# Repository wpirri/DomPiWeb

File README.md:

# DomPiWeb
 Sistema de Domótica con central domiciliaria basada en Raspberry Pi y servicios en la nube para administración externa remota.

 El sistema está formado por una serie de programas en c y c++ que se ejecutan
 dentro del monitor transaccional GMonitor y todo el sistema preparado para
 funcionar en una Raspberry Pi o distribuido entre varias.
 Otro módulo del sistema funciona en un servidor Linux centralizando varios sistemas hogareños permitiendo el acceso remoto a travez de la nube.
 
## Componentes del sistema:
### DomPiWeb: Central domiciliaria de Domótica.
El proyecto contiene distintos programas que se ejecutan como servers dentro de un monitor transaccional GMonitor (https://github.com/wpirri/gmonitor), CGI para hacer de interface con Apache y un micrositio en PHP para la administración local todo este software se ejecuta en una Raspberry Pi. Se incluye además un harware para ser enchufado en el conector de 40 pines de la Raspberry Pi, aprovechar algunos pines de la GPIO y darle alimentación. También se encuentra dentro del proyecto los diseños para imprimir un gabinete para contener la central de domótica y otro para su taería con cargador.

### DomPiIO: Software que permite utilizar la Rasberri Pi como un módulo de expanción de la central de Domótica o como Central de Alarmas integrada al Sistema de Domótica.
El proyecto (https://github.com/wpirri/DomPiIO) contiene distintos programas que se ejecutan como servers dentro de un monitor transaccional GMonitor (https://github.com/wpirri/gmonitor) y CGI para hacer de interface con Apache.

### DomPiClowd: Software que permite controlar los sistemas hogareños desde la nobe.
El proyecto (https://github.com/wpirri/DomPiClowd) contiene distintos programas que se ejecutan como servers dentro de un monitor transaccional GMonitor (https://github.com/wpirri/gmonitor), CGI y un micrositio en PHP para el control de los sistemas de domótica desde un teléfono celular.

### dom32-io-wifi: Harware de módulo de expansió para central de domótica.
El proyecto (https://github.com/wpirri/dom32-io-wifi) está compuesto por un Hardware basado en PIC32 que por medio de servicios REST implementa una interface con la central de domótica DomPiWeb, el firmware necesario y el diseño del gabinete para contenerlo.

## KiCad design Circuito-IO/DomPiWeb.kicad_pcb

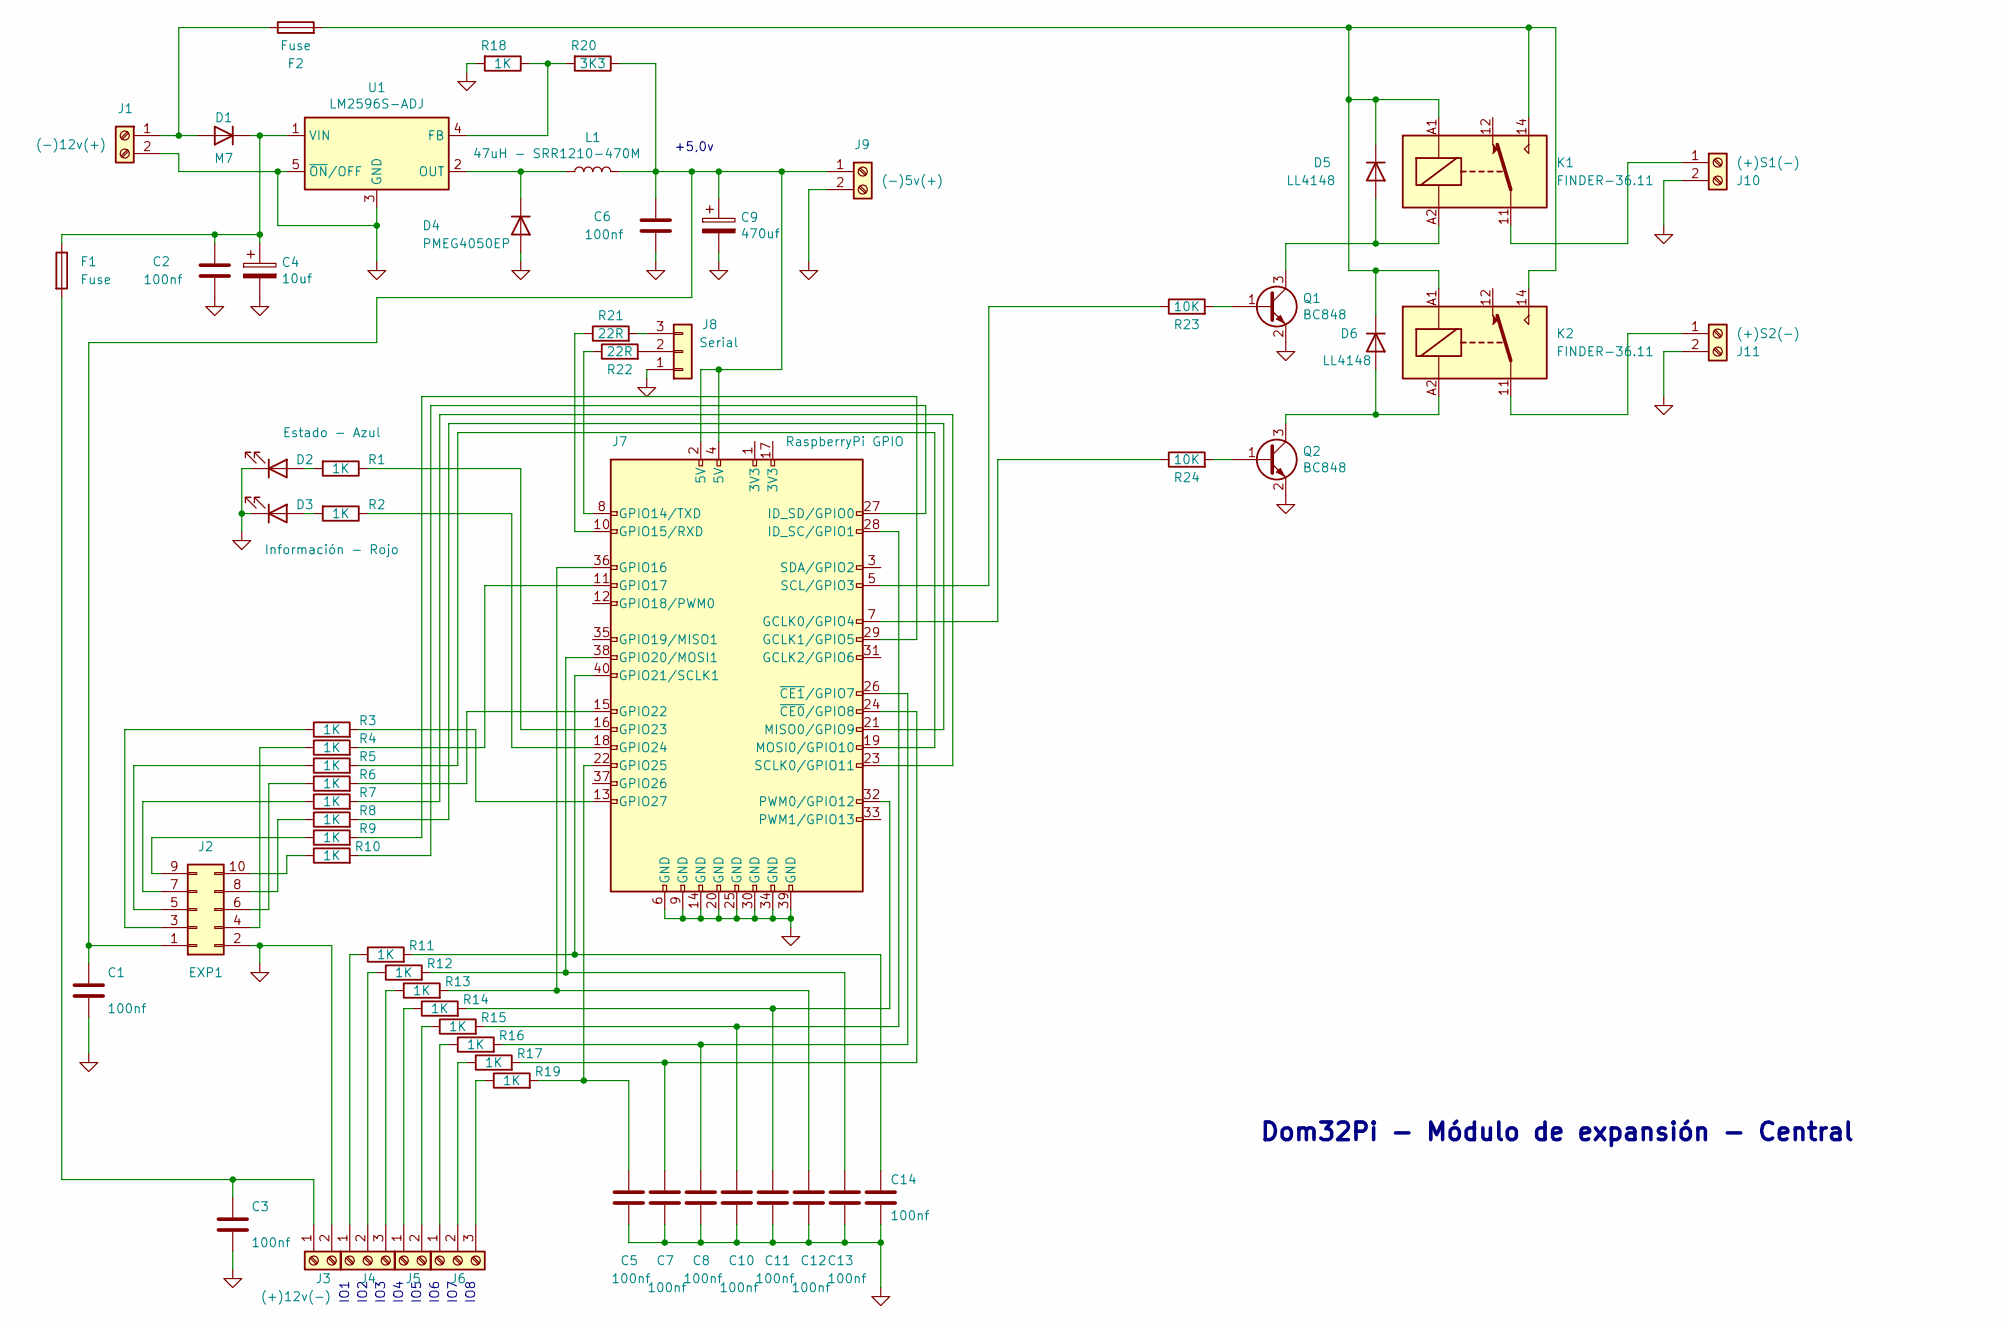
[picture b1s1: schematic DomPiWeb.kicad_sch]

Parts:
C1, C2, C3, C5, C6, C7, C8, C10, C11, C12, C13, C14: 100nf; C_0805_2012Metric_Pad1.18x1.45mm_HandSolder
C4: 10uf; CP_EIA-7343-43_Kemet-X_Pad2.25x2.55mm_HandSolder
C9: 470uf; CP_EIA-7343-43_Kemet-X_Pad2.25x2.55mm_HandSolder
D1: M7; D_SOD-128
D2, D3: Led SMD; LED_1206_3216Metric_Pad1.42x1.75mm_HandSolder
D4: PMEG4050EP; D_SOD-128
D5, D6: LL4148; D_MiniMELF
F1, F2: Fuse; Fuseholder_Cylinder-5x20mm_Schurter_0031_8201_Horizontal_Op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
J1: (-)12v(+); TerminalBlock_Phoenix_PT-1,5-2-5.0-H_1x02_P5.00mm_Horizontal
J2: EXP1; PinHeader_2x05_P2.54mm_Vertical
J3: (+)12v(-); TerminalBlock_Phoenix_PT-1,5-2-5.0-H_1x02_P5.00mm_Horizontal
J4, J6: Bx3; TerminalBlock_Phoenix_PT-1,5-3-5.0-H_1x03_P5.00mm_Horizontal
J5: Bx2; TerminalBlock_Phoenix_PT-1,5-2-5.0-H_1x02_P5.00mm_Horizontal
J7: RaspberryPi GPIO; PinSocket_2x20_P2.54mm_Vertical
J8: Serial; PinHeader_1x03_P2.54mm_Vertical
J9: (-)5v(+); TerminalBlock_Phoenix_PT-1,5-2-5.0-H_1x02_P5.00mm_Horizontal
J10: (+)S1(-); TerminalBlock_Phoenix_PT-1,5-2-5.0-H_1x02_P5.00mm_Horizontal
J11: (+)S2(-); TerminalBlock_Phoenix_PT-1,5-2-5.0-H_1x02_P5.00mm_Horizontal
K1, K2: FINDER-36.11; Relay_SPDT_Finder_36.11
L1: 47uH - SRR1210-470M; L_Bourns_SRR1210A
Q1, Q2: BC848; SOT-23
R1, R2, R3, R4, R5, R6, R7, R8, R9, R10, R11, R12, R13, R14, R15, R16, R17, R18, R19: 1K; R_0805_2012Metric_Pad1.20x1.40mm_HandSolder
R20: 3K3; R_0805_2012Metric_Pad1.20x1.40mm_HandSolder
R21, R22: 22R; R_0805_2012Metric_Pad1.20x1.40mm_HandSolder
R23, R24: 10K; R_0805_2012Metric_Pad1.20x1.40mm_HandSolder
U1: LM2596S-ADJ; TO-263-5_TabPin3

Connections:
GND: C1.2, C2.2, C3.2, C4.2, C5.2, C6.2, C7.2, C8.2, C9.2, C10.2, C11.2, C12.2, C13.2, C14.2, D2.1 (K), D3.1 (K), D4.2 (A), J1.2, J2.2, J3.2, J7.6 (GND), J7.9 (GND), J7.14 (GND), J7.20 (GND), J7.25 (GND), J7.30 (GND), J7.34 (GND), J7.39 (GND), J8.1, J9.2, J10.2, J11.2, Q1.2 (E), Q2.2 (E), R18.2, U1.3 (GND), U1.5 (~ON/OFF)
unnamed: C1.1, C6.1, C9.1, J2.1, J7.2 (5V), J7.4 (5V), J9.1, L1.2, R20.1
unnamed: C2.1, C4.1, D1.1 (K), F1.1, U1.1 (VIN)
unnamed: C3.1, F1.2, J3.1
unnamed: C5.1, J7.22 (GPIO25), R19.2
unnamed: C7.1, J7.24 (~CE0/GPIO8), R17.2
unnamed: C8.1, J7.26 (~CE1/GPIO7), R16.2
unnamed: C10.1, J7.28 (ID_SC/GPIO1), R15.2
unnamed: C11.1, J7.32 (PWM0/GPIO12), R14.2
unnamed: C12.1, J7.36 (GPIO16), R13.2
unnamed: C13.1, J7.38 (GPIO20/MOSI1), R12.2
unnamed: C14.1, J7.40 (GPIO21/SCLK1), R11.2
unnamed: D1.2 (A), F2.1, J1.1
unnamed: D2.2 (A), R1.2
unnamed: D3.2 (A), R2.2
unnamed: D4.1 (K), L1.1, U1.2 (OUT)
unnamed: D5.1 (K), D6.1 (K), F2.2, K1.14, K1.A1, K2.14, K2.A1
unnamed: D5.2 (A), K1.A2, Q1.3 (C)
unnamed: D6.2 (A), K2.A2, Q2.3 (C)
unnamed: J2.3, R3.1
unnamed: J2.4, R4.1
unnamed: J2.5, R5.1
unnamed: J2.6, R6.1
unnamed: J2.7, R7.1
unnamed: J2.8, R8.1
unnamed: J2.9, R9.1
unnamed: J2.10, R10.1
unnamed: J4.1, R11.1
unnamed: J4.2, R12.1
unnamed: J4.3, R13.1
unnamed: J5.1, R14.1
unnamed: J5.2, R15.1
unnamed: J6.1, R16.1
unnamed: J6.2, R17.1
unnamed: J6.3, R19.1
unnamed: J7.5 (SCL/GPIO3), R23.1
unnamed: J7.7 (GCLK0/GPIO4), R24.1
unnamed: J7.8 (GPIO14/TXD), R22.1
unnamed: J7.10 (GPIO15/RXD), R21.1
unnamed: J7.11 (GPIO17), R4.2
unnamed: J7.13 (GPIO27), R3.2
unnamed: J7.15 (GPIO22), R6.2
unnamed: J7.16 (GPIO23), R1.1
unnamed: J7.18 (GPIO24), R2.1
unnamed: J7.19 (MOSI0/GPIO10), R5.2
unnamed: J7.21 (MISO0/GPIO9), R8.2
unnamed: J7.23 (SCLK0/GPIO11), R7.2
unnamed: J7.27 (ID_SD/GPIO0), R10.2
unnamed: J7.29 (GCLK1/GPIO5), R9.2
unnamed: J8.2, R22.2
unnamed: J8.3, R21.2
unnamed: J10.1, K1.11
unnamed: J11.1, K2.11
unnamed: Q1.1 (B), R23.2
unnamed: Q2.1 (B), R24.2
unnamed: R18.1, R20.2, U1.4 (FB)

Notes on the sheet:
IO4
+5,0v
Dom32Pi - Módulo de expansión - Central
IO6
IO5
IO2
IO3
IO1
IO8
IO7

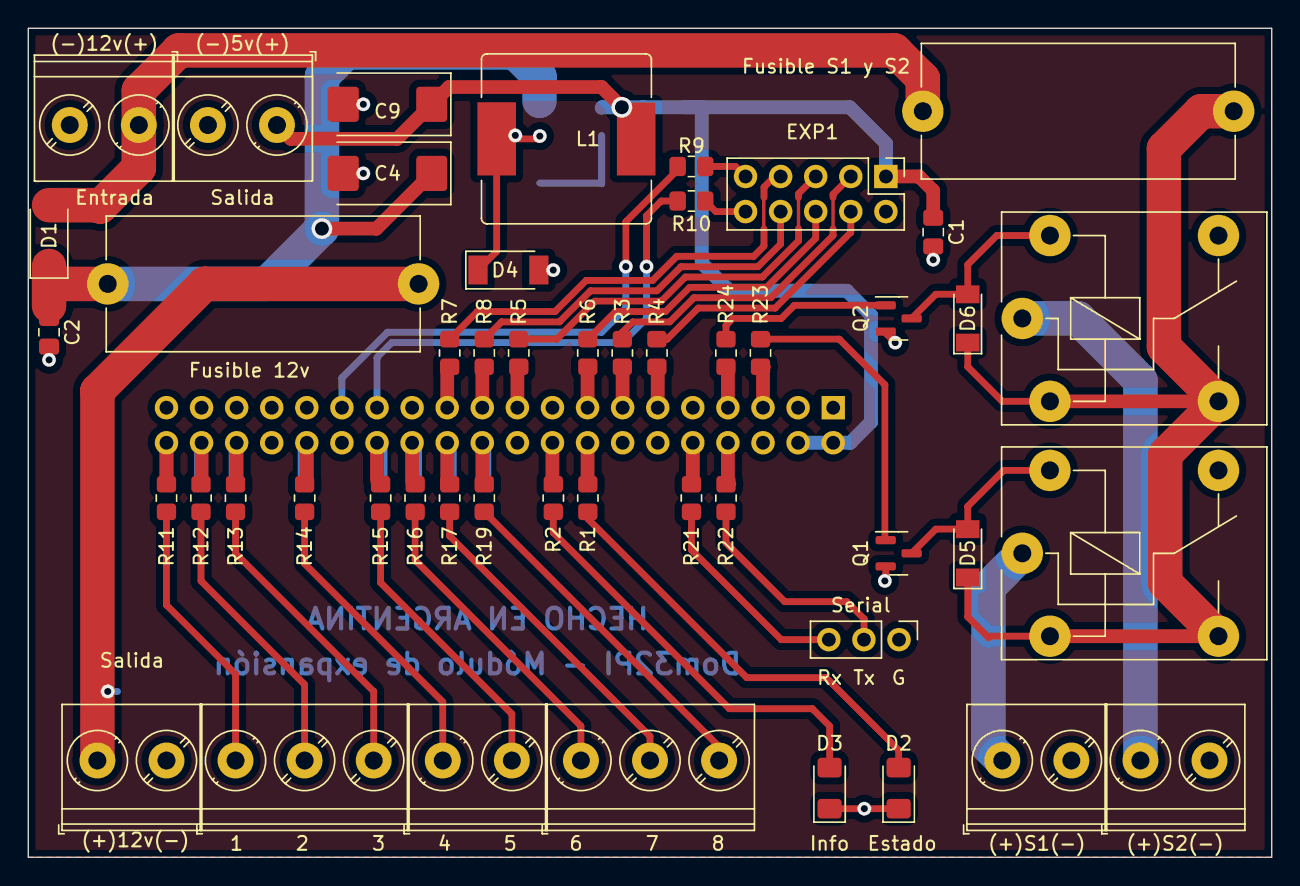
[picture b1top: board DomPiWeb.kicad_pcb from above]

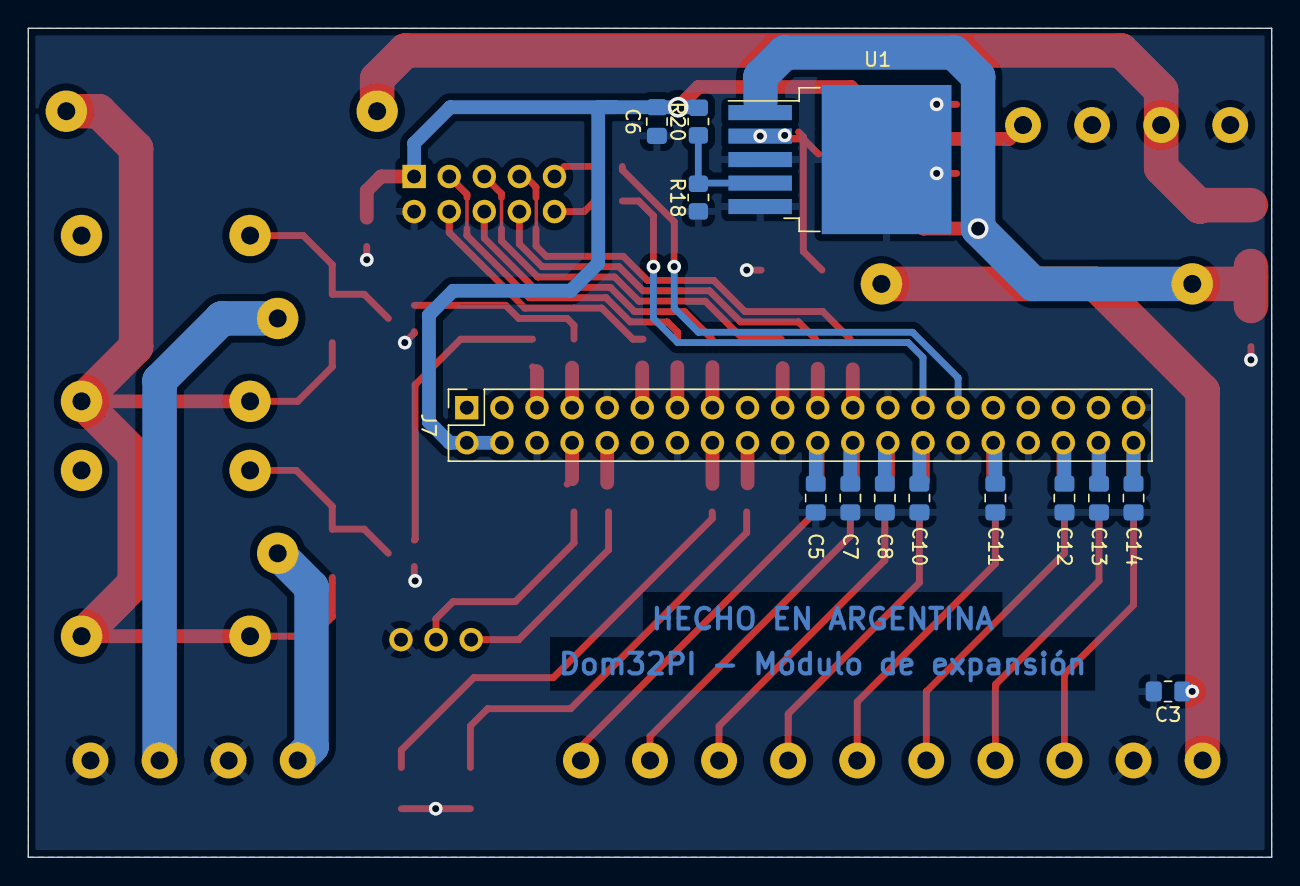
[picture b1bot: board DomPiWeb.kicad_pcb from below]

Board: 2 copper layers, 90.0 x 60.0 mm, 63 parts (14 on the bottom side), 56 nets.

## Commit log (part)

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2021-11-03 Se agrega configuracion de parametros del sistema para interaccion con nube
    Se agrega configuracion de parametros del sistema para interaccion con nube
2021-11-04 Correcciones
    Correcciones
2021-11-15 Manejo de puerto en Raspberry Pi
    Manejo de puerto en Raspberry Pi
2021-11-17 Maquillaje
    Maquillaje
2021-11-20 Comantarios de ayuda al programador
    Comantarios de ayuda al programador
2021-11-23 Soporte HTTPS en mensajeria con nube
    Soporte HTTPS en mensajeria con nube
2021-12-03 Notificacion de cambios
2021-12-08 Cambio de tipo de mensaje de notificacion desde la nube
    Cambio de tipo de mensaje de notificacion desde la nube
2021-12-14 Correcciones del prototipo
    Correcciones del prototipo
2022-02-12 Correcciones a circuito y placa luego de prototipo
    Correcciones a circuito y placa luego de prototipo
2022-05-18 Adaptaciones interface WiFi
    Adaptaciones interface WiFi
2022-05-19 Mejor respuesta de la interface
    Mejor respuesta de la interface
2022-05-25 Soporte wiegan y cola de despacho http
    Soporte wiegan y cola de despacho http
2022-05-30 Correccion de parametro de configuración de sensor de temperatura y humedad
    Correccion de parametro de configuración de sensor de temperatura y humedad
2022-06-11 chmod
    chmod
2022-06-13 Cambio en formato de objetos
    Cambio en formato de objetos
2022-06-15 Cambio en mensajeria de configuracion
    Cambio en mensajeria de configuracion
2022-06-16 Correcciones para evento de pulso
    Correcciones para evento de pulso
2022-06-28 Automatizacion
    Automatizacion
2022-09-05 Update sym-lib-table
2022-09-07 Correcciones a loglevel
    Correcciones a loglevel
2022-09-19 Usando modem GSM USB
    Usando modem GSM USB
2022-10-09 Varios
    Varios
2022-11-11 Mejoras en tiempos de respuesta
    Mejoras en tiempos de respuesta
2022-11-27 Interpretando respuesta
    Interpretando respuesta
2022-12-01 Correcciones al circuito completo de actualización de estado y de configuración
    Correcciones al circuito completo de actualización de estado y de configuración
2022-12-08 Diferencias segun browser instalado
    Diferencias segun browser instalado
2022-12-09 Manejo de modulos perifericos
    Manejo de modulos perifericos
2022-12-20 Imagenes para temperatura
    Imagenes para temperatura
2022-12-28 Correccion por DUMP al reportar un HW desconocido
    Correccion por DUMP al reportar un HW desconocido
2023-02-11 Modificacion para evitar alto consumo de CPU
    Modificacion para evitar alto consumo de CPU
2023-02-17 Correcciones a la Base e inicialización
    Correcciones a la Base e inicialización
2023-02-17 Generación de distribución para instalación y upgrade
    Generación de distribución para instalación y upgrade
2023-02-18 Correccion en timeout de conexión
    Correccion en timeout de conexión
2023-02-18 Se agrega un defina para poner en debug la clase TCP
    Se agrega un defina para poner en debug la clase TCP
2023-02-22 Se agregan las direcciones de las centrales a la configuración y se hacen correcciones de capitalización en nombres de columnas
    Se agregan las direcciones de las centrales a la configuración y se hacen correcciones de capitalización en nombres de columnas
2023-02-22 Se agrega la respuesta a los POST (tipo MSG) que no hace falta pero ahorra tiempo
    Se agrega la respuesta a los POST (tipo MSG) que no hace falta pero ahorra tiempo
2023-02-22 Archivos de instalación y upgrade eliminados del repositorio
    Archivos de instalación y upgrade eliminados del repositorio
2023-02-22 Emprolijado de ABM
    Emprolijado de ABM
2023-02-25 Correccion de envío de configuración
    Se evita enviar la configuración a un dispositivo que no está conectado
2023-02-25 Scroll de la planta
    Scroll de la planta
2023-02-28 Muchos cambios
    Correcciones en formularios que fallaba en onload
    Se emprolija el server poniendo dentro de funciones cosas que estaban en el main
    Se fracciona por problemas de tamaño la mensajería con la nube
    Se agrega el listado multiple a las funciones de JavaScript
2023-03-01 Cambio de motor de base de datos
    Se cambia el uso de SQL Lite a MySQL por problemas con control de integridad referencial y mezcla de datos entre tablas
2023-03-06 Manejo de automatizacion
    Automatización de eventos con entradas analoficas (Iluminación)
2023-03-08 Reestructuración
    Se mueven todos los servicios de ABM a un server aparte para separarlos de los servicios de control. Además se corrigen los mensajes que estaban con Post y debían ser Notify para un correcto funciona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
2023-03-10 Nuevas imágenes
    Nuevas imágenes
2023-03-10 Se eliminan algunos warning de compilación
    Se eliminan algunos warning de compilación
2023-03-10 No va en el repositorio
    No va en el repositorio
2023-03-19 Aumento del tiempo de refresco de pantalla de espera
    Aumento del tiempo de refresco de pantalla de espera
2023-03-23 Nueva placa
    Nueva placa
2023-03-24 PCB completo
    PCB completo. Con cambios en leyendas y en el esquema para simplificar el PCB
2023-03-25 Correcciones de estética
    Correcciones de estética
2023-04-06 Correcciones para la generacion correcta de vista 3D
    Correcciones para la generacion correcta de vista 3D
2023-04-06 Gabinete para bateria y cargador
    Gabinete para bateria y cargador
2023-04-06 Server eliminado
    Server eliminado
2023-04-06 Se iguala la comunicacion con RBPi a la del modulo WiFi
    Se iguala la comunicacion con RBPi a la del modulo WiFi
2023-04-21 Se actualiza la vista montada
    Se actualiza la vista montada
2023-04-21 Archivo de la versión anterior de KiCAD
    Archivo de la versión anterior de KiCAD
2023-05-02 ABM Alarma
    ABM Alarma
2023-05-07 Cambio de ubicación
    Cambio de ubicación
2023-05-09 Sincronizacion de datos de usuarios para acceso desde la app
    Sincronizacion de datos de usuarios para acceso desde la app
2023-05-11 Ventana de ABM mas ancha
    Ventana de ABM mas ancha
2023-05-18 Se agrega el grupo visual de riego
    Se agrega el grupo visual de riego
2023-05-18 Cambio de iconos
    Cambio de iconos
2023-05-22 Se agrega estado de alarma a la tabla de particiones
    Se agrega estado de alarma a la tabla de particiones
2023-05-24 Fondo transparente
    Fondo transparente
2023-05-24 Indices
    Indices
2023-05-27 Script y query para hacer backup de la base
    Script y query para hacer backup de la base
2023-05-30 Correccion en envio de configuracion a WiFi
    Cuando los campos están en NULL se enviaba "NULL" y si estaba vacío no se enviaba. Se cambió para que en caso de vacío o NULL se envíe una cadena de tamaño cero
2023-06-05 Update README.md
    Se completa la descripción
2023-06-17 Funcionalidad de upgrade via formulario web
    Funcionalidad de upgrade via formulario web
2023-07-17 Se mantienen aparte las alteraciones a la base de datos
    Se mantienen aparte las alteraciones a la base de datos
2023-07-26 Correcciones de instalación
    Correcciones de instalación
2023-08-21 Errores encontrados en generacion de dump
    Errores encontrados en generacion de dump
2023-08-22 se mueve el objeto GEvent a la parte compartida
    se mueve el objeto GEvent a la parte compartida
2023-09-01 Mejor logueo de eventos y correccion en suscripciones
    Mejor logueo de eventos y correccion en suscripciones
2023-09-09 Alarma y SMS en SAF
    Alarma y SMS en SAF
2023-09-13 Implementación de SAF para los mensajes a la nube
    Implementación de SAF para los mensajes a la nube
2023-09-24 Defines para exclusion de modulos
    Sincronización A/A y la alarma integrada definidos como módulos que se incluyen o no en el momento de la compilación para poder seguir sacando actualizaciones del resto del sistema apagando estos mód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
2023-10-14 Imagenes de ventilador
    Imagenes de ventilador
2023-10-14 Tamaño icono
    Icono mas pequeño
2023-10-16 Correcciones en notificacion a la nube
    Se notifican los cambios de assign cuando se crean o editan
2023-10-23 Correccion de envio de pulso
    Correccion de envio de pulso
2023-11-06 Correcciones de backup
    Correcciones de backup
2023-11-18 Soporte camaras rtsp
    Soporte camaras rtsp
2023-12-10 Update gmond
2023-12-24 Modulo Alarma
    Modulo Alarma
2023-12-28 Se agrega dompi_gpio y sus cgi
    Se agrega dompi_gpio y sus cgi
2024-01-03 Desarrollo de alarma
    Desarrollo de mas funicionalidades del modulo de alarmas y correcciones en la implementación de TCP
2024-01-10 Modulo de alarmas
    Actualización de estado de alarma en la nube
2024-01-22 San Bernardo 2024
    San Bernardo 2024
2024-01-29 Se agrega un retardo entre la deteccion del archivo de actualización y su procesamiento
    Se agrega un retardo entre la deteccion del archivo de actualización y su procesamiento
2024-01-31 Correccion en listado
    Correccion en listado
2024-02-11 Acomodando Javascript
    Acomodando Javascript
2024-02-25 Revert "Ultimos cambios"
    This reverts commit 173d3c8938142ac584b2bd8d9c4193b61de6ace6.
2024-02-25 Revert "Acomodando Javascript"
    This reverts commit aaeb44c40535f88fec81ebb8355fad20554498c4.
2024-02-25 Revert "Correccion en listado"
    This reverts commit fbed0e2599dca01e317d24d7900e6eef4794eadc.
2024-02-25 Revert "Se agrega un retardo entre la deteccion del archivo de actualización y su procesamiento"
    This reverts commit 87a93e2e5289ef509aa2b0603d1ce87e5e2d6928.
2024-02-26 Corecciones, info de hardware, parametros
    Corecciones, info de hardware, parametros
2024-02-28 COntrol de alarma
    COntrol de alarma
2024-03-08 Correccion en el formato de respuesta
2024-03-11 Dropdown para Horas y Minutos en varios ABM
    Dropdown para Horas y Minutos en varios ABM
2024-04-03 Mejoras de respuesta y detección de placas online
    Se agrega fecha y hora en las respuestas del servicio de estado
    Se cambia el tiempo que se toma para marcar una placa como off-line, ahora depende de la configuración.
2024-05-08 Detección de versión de firmware
    Detección de versión de firmware
2024-05-11 Formulario de upload
    Formulario de upload
2024-05-16 Soporte para compilacion en multiples plataformas
    Soporte para compilacion en multiples plataformas
2024-05-19 Correcciones en la instalación
    Correcciones en la instalación
2024-06-14 Correccion en rotacion de host de nube
    Correccion en rotacion de host de nube
2024-07-30 Correcciones de update de firmware y configuracion
    Correcciones de update de firmware y configuracion
2024-10-23 Capturas de configuración de MCC
    Capturas de configuración de MCC
2024-10-31 Se agrega reconocimiento de interface touch
    Se agrega reconocimiento de interface touch
2024-11-04 Solicitud de download
    Solicitud de download
2024-12-03 Sincronizacion de grupo
    Sincronizacion de grupo
2024-12-27 Actualizaciones para interface touch
    Se modifica la respuesta de los servicios de control de objetos para que devuelvan en formato de formulario
    Se modifica el script sniffer de archivos subidos para soportar todos los .hex
2025-02-01 Propagacion de grupos
    Propagacion de grupos y redistribucion de servicios
2025-03-27 Nuevo release por cambios en la nube
    Nuevo release por cambios en la nube
2025-03-31 Vuelta atras del server de tareas
    Vuelta atras del server de tareas. Se devuelven las funcionalidades a dompi_server
2025-04-03 Correcciones para A/A
    Correcciones para A/A
2025-04-07 Vuelta atras a version estable
    Vuelta atras a version estable
2025-05-02 Correcciones a backup y reinicio
    Correcciones a backup y reinicio
2025-06-12 Configuracion de pantallas de dispositivos touch
    Configuracion de pantallas de dispositivos touch
2025-06-13 Generacion de archivo de listado para update
    Generacion de archivo de listado para update
2025-06-21 Listado de distribución
    Se ordena y eliminan los duplicados en el listado de distribución de archivos de las pantallas de los teclados touch
2025-07-11 Nueva pantalla de inicio
    Nueva pantalla de inicio
2025-07-25 Tiempo del wait y control de tiempo de ejecución
    Tiempo del wait y control de tiempo de ejecución
2025-08-10 Se corrige un delay en la actualización con la nube
    Se corrige un delay en la actualización con la nube
2025-09-28 Revisión de código
    Revisión de código
2025-10-04 Mejora del help
    Mejora del help
2025-10-06 Correccion en la llamada a un servicio
    Correccion en la llamada a un servicio
2025-10-15 Mejora en consumo de CPU de dompi_server
    Mejora en consumo de CPU de dompi_server
2025-10-26 Correcciones en init de base
    Correcciones en init de base
2025-11-09 Mejora en tiempos de loop de dompi_server
    Mejora en tiempos de loop de dompi_server
2025-11-12 Cron corregido e info del clima
    Cron corregido e info del clima
2025-11-12 Correccion de instalador
    Correccion de instalador
